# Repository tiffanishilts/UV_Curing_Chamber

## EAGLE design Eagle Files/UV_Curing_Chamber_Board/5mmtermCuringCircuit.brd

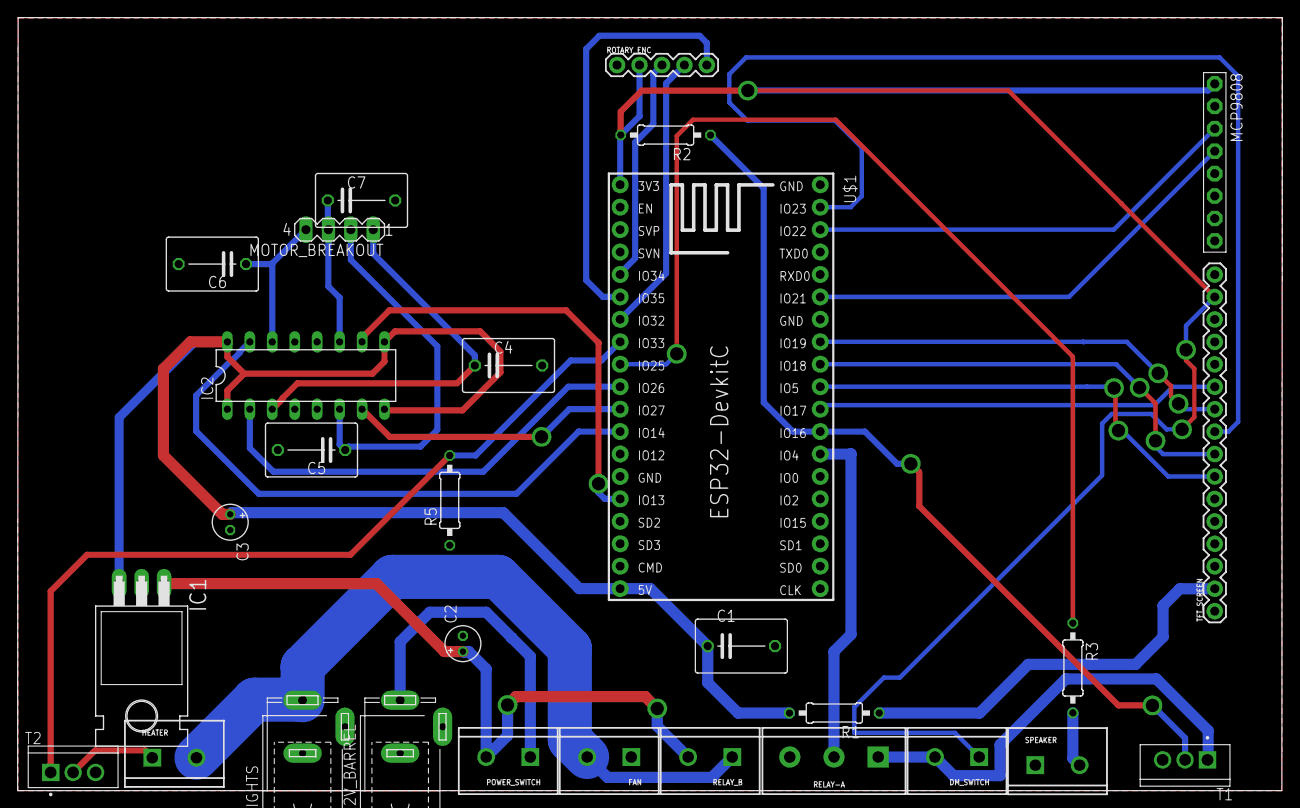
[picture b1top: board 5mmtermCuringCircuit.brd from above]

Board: 2 copper layers, 143.2 x 87.5 mm, 29 parts (0 on the bottom side), 32 nets.

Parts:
12V_BARREL: SPC4077
C1: .1uF; C075-063X106
C2, C3: 10uF; E1,8-4
C4, C5, C6, C7: 0.1u; C075-063X106
DM_SWITCH: SCREWTERMINAL-5MM-2
FAN: SCREWTERMINAL-5MM-2
HEATER: SCREWTERMINAL-5MM-2
IC1: 7805T; TO220H
IC2: L293D; DIL16
LIGHTS: SPC4077
MCP9808: 1X08-BIG
MOTOR_BREAKOUT: MA04-1
POWER_SWITCH: SCREWTERMINAL-5MM-2
R1, R3: 220; 0207/10
R2, R5: 10k; 0207/10
RELAY-A: SCREWTERMINAL-5MM-3
RELAY_B: SCREWTERMINAL-5MM-2
ROTARY_ENC: 1X05
SPEAKER: SCREWTERMINAL-5MM-2
T1, T2: RFP30N06LE; TRANS_RFP30N06LE
TFT_SCREEN: 1X16
U$1: ESP32DEVKITC; ESP32-DEVKITC

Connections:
+3V3: DM_SWITCH.1, MCP9808.1, R2.2, ROTARY_ENC.2, TFT_SCREEN.15, U$1.1
+5V: C1.1, C3.+, IC1.3, IC2.1, IC2.8, IC2.9, IC2.16, R1.2, U$1.19
GND: 12V_BARREL.1, C1.2, C2.-, C3.-, C4.2, C5.2, C6.2, C7.2, FAN.1, IC1.2, IC2.4, IC2.5, IC2.12, IC2.13, LIGHTS.1, MCP9808.2, R5.1, RELAY-A.3, ROTARY_ENC.1, SPEAKER.1, T1.3, T2.3, TFT_SCREEN.1, TFT_SCREEN.16, U$1.14, U$1.32, U$1.38
unnamed: TFT_SCREEN.9, U$1.37
unnamed: IC2.15, U$1.12
unnamed: 12V_BARREL.3, POWER_SWITCH.1
unnamed: HEATER.1, T2.2
unnamed: IC2.7, U$1.11
unnamed: R3.2, SPEAKER.2
unnamed: C5.1, IC2.6, MOTOR_BREAKOUT.2
unnamed: DM_SWITCH.2, RELAY-A.1, T1.1
unnamed: R2.1, T1.2, U$1.27
unnamed: MCP9808.3, U$1.36
unnamed: MCP9808.4, U$1.33
unnamed: IC2.2, U$1.10
unnamed: R5.2, T2.1, U$1.8
unnamed: C4.1, IC2.3, MOTOR_BREAKOUT.1
unnamed: RELAY-A.2, U$1.26
unnamed: R1.1, TFT_SCREEN.2
unnamed: ROTARY_ENC.3, U$1.5
unnamed: ROTARY_ENC.4, U$1.7
unnamed: ROTARY_ENC.5, U$1.6
unnamed: TFT_SCREEN.11, U$1.28
unnamed: TFT_SCREEN.10, U$1.31
unnamed: C7.1, IC2.11, MOTOR_BREAKOUT.3
unnamed: TFT_SCREEN.8, U$1.30
unnamed: TFT_SCREEN.7, U$1.29
unnamed: R3.1, U$1.9
unnamed: C6.1, IC2.14, MOTOR_BREAKOUT.4
unnamed: FAN.2, HEATER.2, LIGHTS.3, RELAY_B.1
unnamed: IC2.10, U$1.15
V+: C2.+, IC1.1, POWER_SWITCH.2, RELAY_B.2

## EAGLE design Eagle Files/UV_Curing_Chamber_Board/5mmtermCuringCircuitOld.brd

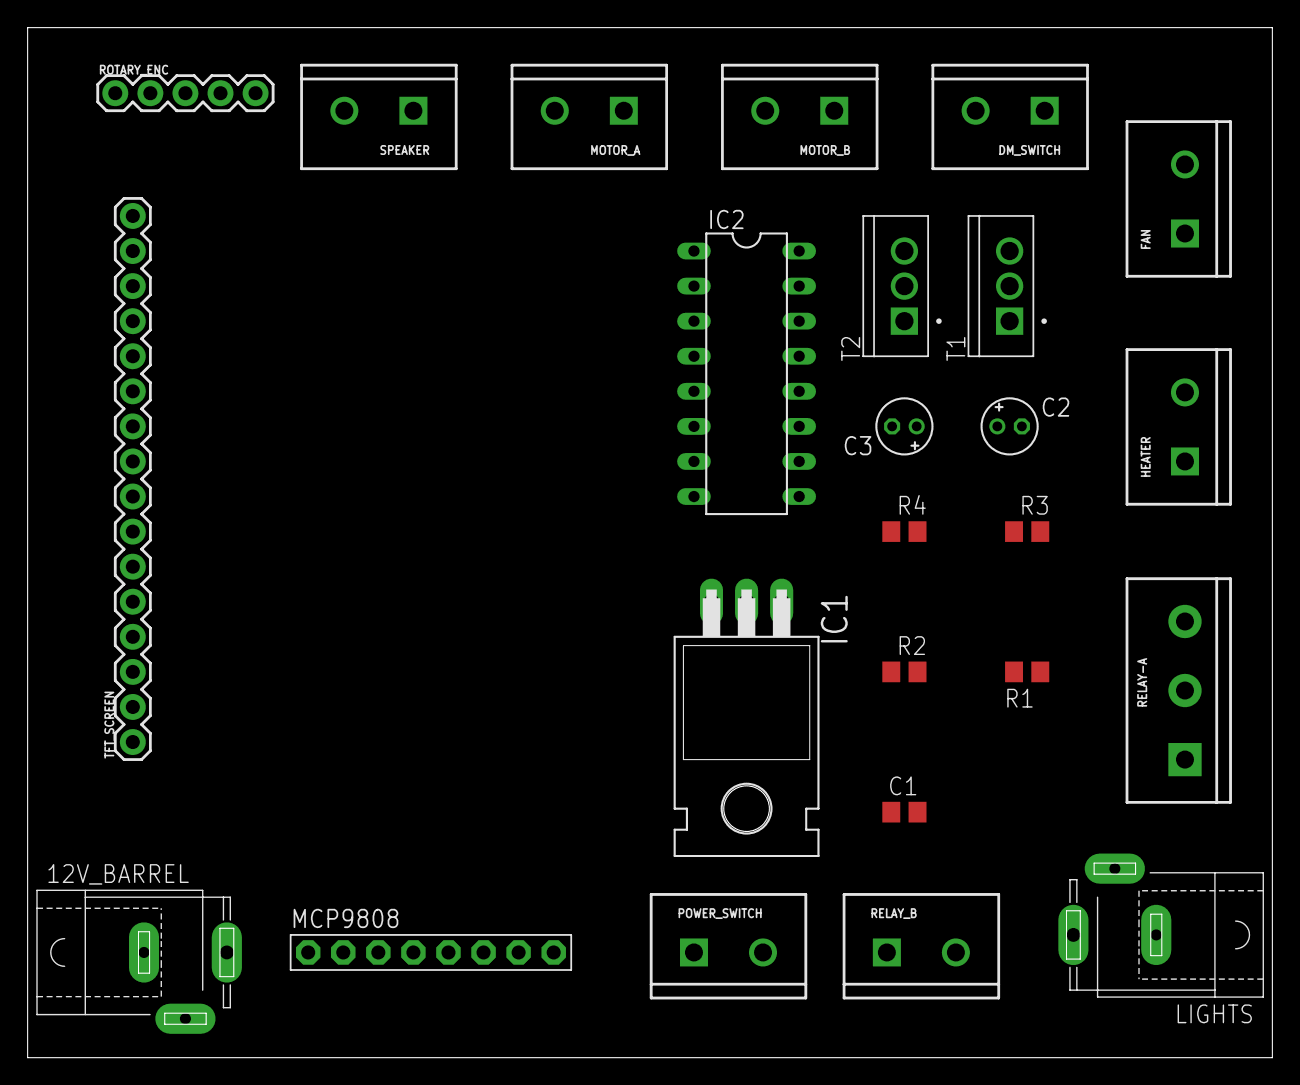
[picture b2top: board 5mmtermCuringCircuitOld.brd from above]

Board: 2 copper layers, 90.2 x 74.6 mm, 25 parts (0 on the bottom side), 17 nets, no tracks yet.

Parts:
12V_BARREL: SPC4077
C1: 0.1uF; C0805
C2, C3: 10uF; E1,8-4
DM_SWITCH: SCREWTERMINAL-5MM-2
FAN: SCREWTERMINAL-5MM-2
HEATER: SCREWTERMINAL-5MM-2
IC1: 7805T; TO220H
IC2: L293D; DIL16
LIGHTS: SPC4077
MCP9808: 1X08-BIG
MOTOR_A: SCREWTERMINAL-5MM-2
MOTOR_B: SCREWTERMINAL-5MM-2
POWER_SWITCH: SCREWTERMINAL-5MM-2
R1, R2: 10K; R0805
R3, R4: 220; R0805
RELAY-A: SCREWTERMINAL-5MM-3
RELAY_B: SCREWTERMINAL-5MM-2
ROTARY_ENC: 1X05
SPEAKER: SCREWTERMINAL-5MM-2
T1, T2: RFP30N06LE; TRANS_RFP30N06LE
TFT_SCREEN: 1X16

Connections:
12V: C2.+, IC1.1, POWER_SWITCH.2, RELAY_B.2
GND: 12V_BARREL.1, C1.2, C2.-, C3.-, FAN.1, IC1.2, IC2.4, IC2.5, IC2.12, IC2.13, LIGHTS.1, MCP9808.2, R1.1, RELAY-A.3, ROTARY_ENC.1, SPEAKER.1, T1.3, T2.3, TFT_SCREEN.1, TFT_SCREEN.16
unnamed: C1.1, C3.+, IC1.3, IC2.16, R3.2
unnamed: IC2.1, IC2.9
unnamed: 12V_BARREL.3, POWER_SWITCH.1
unnamed: HEATER.1, T2.2
unnamed: R1.2, T2.1
unnamed: R4.2, SPEAKER.2
unnamed: DM_SWITCH.1, MCP9808.1, R2.2, ROTARY_ENC.2, TFT_SCREEN.15
unnamed: DM_SWITCH.2, RELAY-A.1, T1.1
unnamed: R2.1, T1.2
unnamed: IC2.3, MOTOR_A.2
unnamed: IC2.6, MOTOR_A.1
unnamed: R3.1, TFT_SCREEN.2
unnamed: IC2.14, MOTOR_B.1
unnamed: IC2.11, MOTOR_B.2
RELAY_NO: FAN.2, HEATER.2, IC2.8, LIGHTS.3, RELAY_B.1

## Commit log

2019-02-16 Add all
2019-02-27 I don't know what I'm doing.
2019-05-21 Updating Project to most recent
2019-05-28 Added Preliminary Stepper Code to Main.ino
2019-05-30 House keeping, deleting unneeded files and reorganizing file structure
2019-05-30 House Keeping
2019-06-03 More House Keeping/deleting unnecessary files
2019-06-19 Pulling?
2019-06-19 Added Prototype Stepper Code
2019-06-19 Cleanup
2019-06-19 Removing Items
2019-06-26 Adding Eagle Files
2019-07-10 started cleaning up board sch and deleted old rev of board
2019-07-10 more eagle
2019-07-17 deleted redundant files
2019-07-17 schematic
2019-07-17 board updates
2019-07-24 Added ESP32 Eagle Library
2019-07-24 removed unnecesary files
2019-07-24 more unfucking schematic
2019-07-24 Fixed incorrect connections on Eagle Schematic
2019-07-24 Added bypass caps to stepper outputs.
2019-07-24 Updating?
2019-07-24 Fixed Error keeping us from opening schematic by deleting a bunch of code.
2019-07-31 Fixed Eagle
2019-08-07 finished preliminary design for eagle board, awaiting review from chuck
2019-08-14 Changes to the Curing Chamber Code
2019-08-14 fixing board
2019-08-14 Power changes to motor chip
2019-08-21 Changes to the board and generated CAM files
2019-08-21 Updating with CAM stuff
2019-10-02 Adding new Boards
2019-10-02 newbottomboard.brd design
2019-10-02 Removing extra Files
2019-10-02 Added more labels to newbottomboard.brd
2019-10-02 fixed errors on v3 board
2019-10-18 updating v3 board

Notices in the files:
parts and their libraries:
SparkFun-Connectors: Licensing: Creative Commons ShareAlike 4.0 International - https://creativecommons.org/licenses/by-sa/4.0
